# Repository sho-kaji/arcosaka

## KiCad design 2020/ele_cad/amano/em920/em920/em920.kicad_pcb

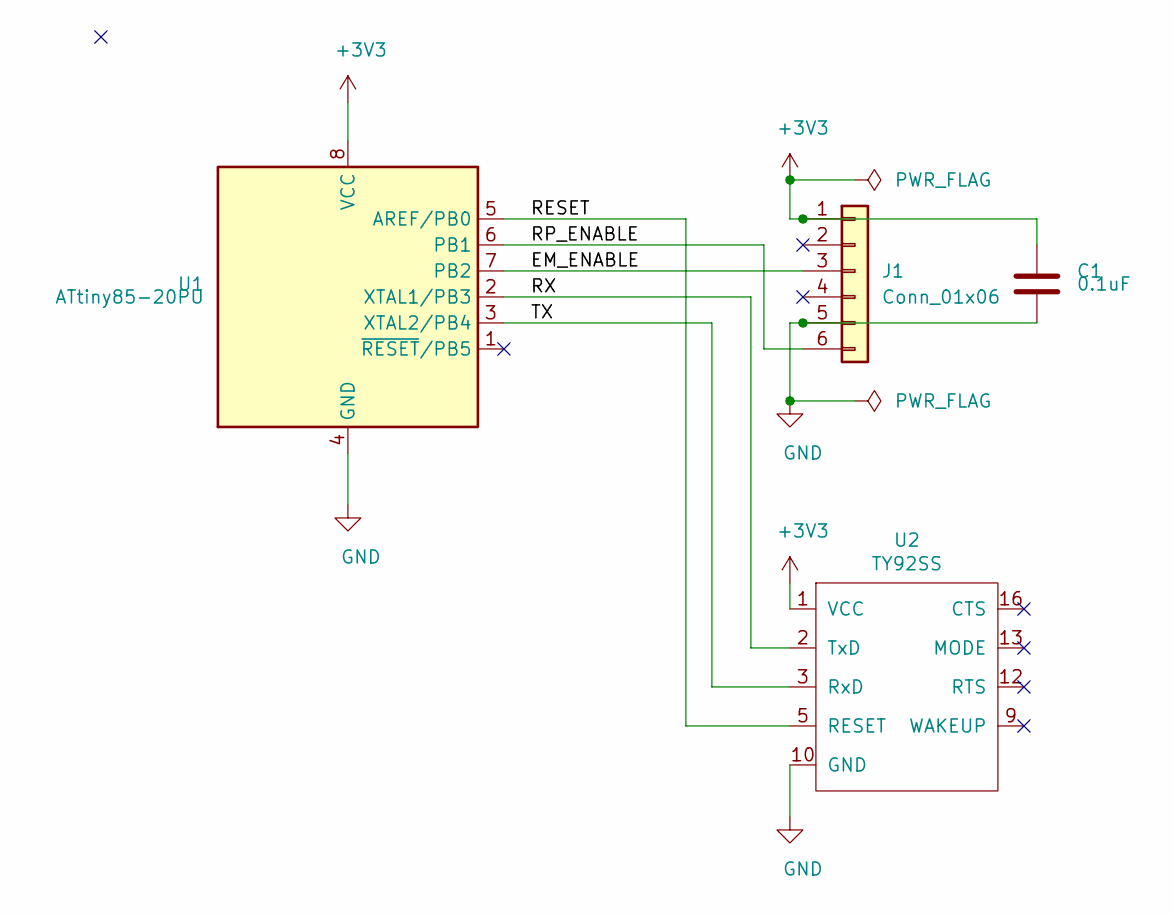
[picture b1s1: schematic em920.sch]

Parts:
C1: 0.1uF; C_Disc_D3.0mm_W1.6mm_P2.50mm
J1: Conn_01x06; PinHeader_1x06_P2.54mm_Vertical
U1: ATtiny85-20PU; DIP-8_W7.62mm
U2: TY92SS

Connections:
+3V3: C1.1, J1.1, U1.8 (VCC), U2.1 (VCC)
/EM_ENABLE: J1.3, U1.7 (PB2)
/RESET: U1.5 (AREF/PB0), U2.5 (RESET)
/RP_ENABLE: J1.6, U1.6 (PB1)
/RX: U1.2 (XTAL1/PB3), U2.2 (TxD)
/TX: U1.3 (XTAL2/PB4), U2.3 (RxD)
GND: C1.2, J1.5, U1.4 (GND), U2.10 (GND)

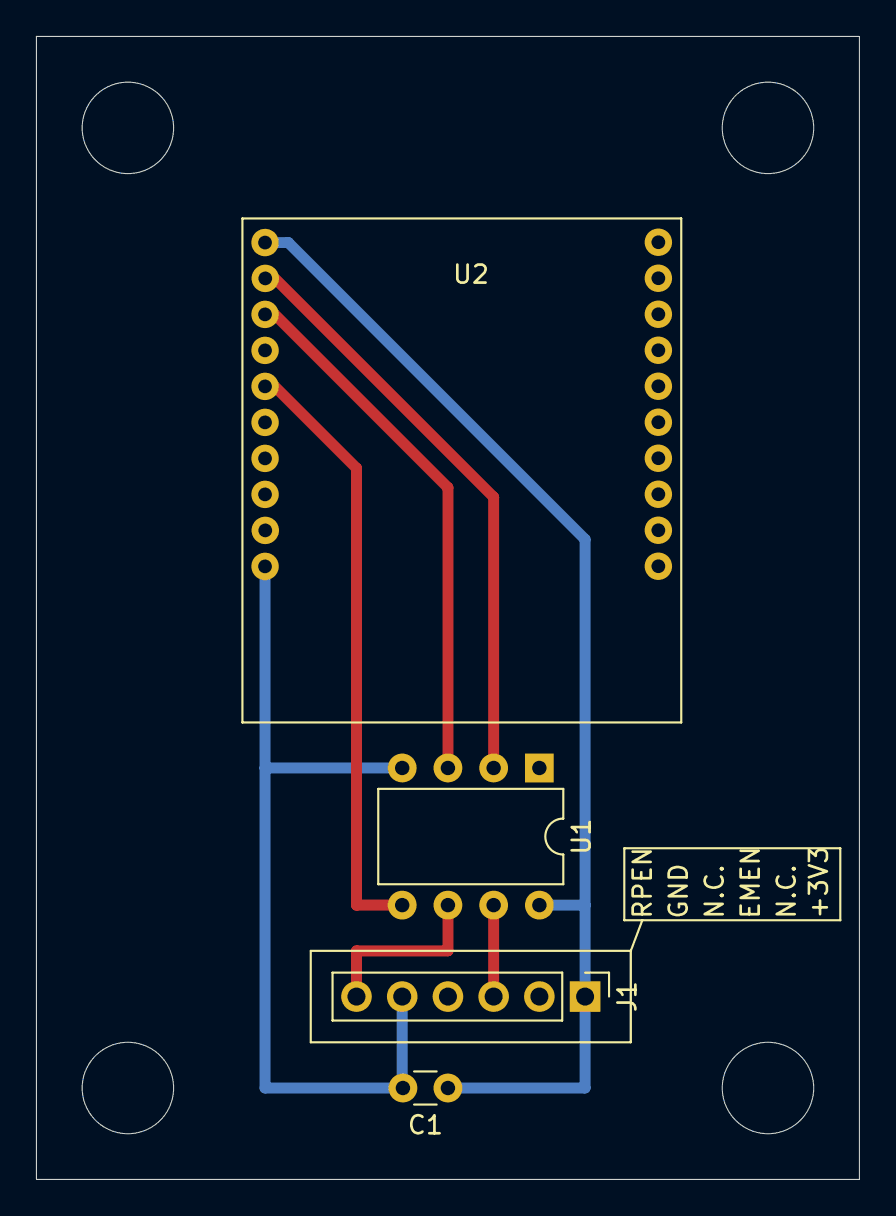
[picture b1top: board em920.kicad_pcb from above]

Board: 2 copper layers, 45.7 x 63.5 mm, 4 parts (0 on the bottom side), 7 nets.

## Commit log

2018-11-12 .gitignore 変更
2018-11-12 2018 最終版
2018-11-22 ポチのコード(らしきもの)をコミット
2019-04-27 1904272229
2019-04-28 去年のコードから自動シャットダウンスクリプトをコピー
2019-04-28 インストールスクリプト追加
2019-04-28 ROSインストールスクリプト修正
2019-04-28 ROS melodic インストールスクリプト修正
2019-04-28 スタートアップスクリプトを修正
2019-04-28 ros-melodic-desktop-full にて作成
2019-04-28 コーディングルールをreadme.txtに記載
2019-04-29 テスト用ros環境作成スクリプト
2019-04-29 テスト環境追加
2019-04-29 インストールと初期設定スクリプトをshに移動 起動スクリプトを追加
2019-04-30 test_webrtcのテスト
2019-04-30 test_webrtc monoを追加
2019-04-30 test_webrtc momoを追加/テスト成功
2019-04-30 ros_run.shを修正
2019-04-30 ファイル権限を追加
2019-04-30 ros_set.shを追加
2019-04-30 ros_setprg.shを追加
2019-04-30 test_webrtcを修正
2019-05-01 test_webrtcを修正2
2019-05-01 test_opencvを作成しようとした
2019-07-17 readmeを少し追記
2019-07-23 案山子フォルダを削除
2019-07-27 test
2019-08-14 ros_set.shの更新
2019-08-14 とりあえずテスト用に去年のarm.pyを入れてみる
2019-08-18 ros-pwm-pca9685をサブモジュールに追加
2019-09-01 とりあえず環境リセット
2019-09-01 フォルダとファイルを再構築
2019-09-01 ros_set.sh 修正
2019-09-01 ros_set.sh 修正2
2019-09-01 catkin_make修正
2019-09-01 ros_set修正3
2019-09-03 hand.py body.py テンプレート作成
2019-09-04 パッケージ名変更
2019-09-04 モーターの定数を各制御に移動
2019-09-07 arm ポート指定方法の変更
2019-09-07 arm.py 改造中
2019-09-09 コードの変更
2019-09-15 brain追加(初期化まで)
2019-09-15 不要ファイル削除
2019-09-15 モーター制御用のクラスを追加 mortor.py mortor_consts.py
2019-09-15 abh.launch 修正
2019-09-15 brain骨組み実装
2019-09-16 競合するファイルを削除
2019-09-16 実行権限付与
2019-09-16 windows用のpythonファイル実行権限スクリプト
2019-09-16 pythonのパスを指定し直し
2019-09-16 改行コード変更
2019-09-16 pythonのバージョン変更
2019-09-16 python2に合わせて修正(1)
2019-09-18 armテスト用にファイル追加
2019-09-21 モーターのテストプログラムコミット
2019-09-21 少し更新
2019-09-21 mortor_test.py 実行権限付与
2019-09-21 mortor_test 改良
2019-09-21 mortor.py 更新
2019-09-21 制限解除フラグを追加(主にテスト用)
2019-09-22 mortor 40Kのサーボつないだ
2019-09-22 doubleからintに変え忘れ
2019-09-22 DCモーター用プログラム修正
2019-09-22 DCモーター用テスト
2019-09-22 DCモーター用関数修正
2019-09-22 mortor DC用に修正
2019-09-22 mortor_const DCモーター用に調整
2019-09-22 DCモーター用
2019-09-22 DCモーター用2
2019-09-22 いろいろ更新
2019-09-22 電圧測定を追加
2019-09-22 電圧測定の権限を更新
2019-09-22 nemui
2019-09-22 やる気をなくした
2019-09-22 mortor.pyのバグ取り
2019-09-23 ステッピングモーター動いた
2019-09-23 brain動作実装(poll検出未対応)
2019-09-23 DCモーター刈リン様用テスト
2019-09-23 arm製作中
2019-09-23 param更新
2019-09-23 改行コード修正->LF
2019-09-23 arm修正
2019-09-23 mortor_test.pyで足回りテストを実行
2019-09-24 DCモーターの定数を実測したものに変更
2019-09-24 arm body hand 全面書き換え
2019-09-25 brain構文エラー修正
2019-09-26 電流測定/abhのメッセージ処理変更
2019-09-26 eyes.py コミット
2019-09-26 abhを変更
2019-09-26 実行権限付与(いつも忘れる)
2019-09-26 先頭を「#!/usr/bin/env python」に変更
2019-09-26 body_const更新
2019-09-26 芽かきと収穫の動作を追加
2019-09-26 brain ポール検出時動作追加、コメント追加、バグ修正
2019-09-26 brain バグ修正
2019-09-26 eye 先頭コメント追加
2019-09-27 とりあえずコミット
2019-09-27 とりあえず動いたから更新
2019-09-27 ina226電流測定追加
2019-09-27 brainバグ修正
2019-09-27 brain バグ修正、デバッグモードコメント追加
2019-09-27 ダミーclient追加
2019-09-28 arm body handを統合
2019-09-28 abh_constsの実行権限付与
2019-10-04 eye通信部分実装(仕組みのみ)
2019-10-04 モーター制御の微調整
2019-10-05 360サーボのテスト用
2019-10-05 電流電圧測定修正
2019-10-05 距離センサーテストモジュール追加
2019-10-05 python2.7では精度が出ない
2019-10-05 電圧低下時の動作を追加
2019-10-05 ミス修正
2019-10-05 シャットダウン判定修正
2019-10-12 debug Arm用部分だけ作成しました。
    下記をinstallしてください
    sudo apt-get instgall ros-melodic-roswww
    その後、catkin_makeしてください。
    下記を実行してください
    roslaunch arc2019 client.launch
    下記アドレスにアクセスしてください。
2019-10-13 コメント追加
2019-10-13 電流電圧をbodyから流せるように変更
2019-10-13 今日の作業をコミット
2019-10-13 今日の作業をコミット2
2019-10-14 各センサーがついていない場合にデバッグモードで動くようにした(はず)
2019-10-15 camera画像が映るようにしました。
    1.mjpg-streamerをinstallしてください。
    手順
    $ git clone https://github.com/jacksonliam/mjpg-streamer.git
    $ cd mjpg-streamer/mjpg-streamer-experimental
    $ make
    $ sudo make install
2019-10-15 コミット漏れファイルを追加
2019-10-15 コミット漏れ2
2019-10-15 mortor.py 変更
2019-10-15 mortor.pyの関数を変更
2019-10-18 eventemitter2.min.js roslib.min.js をサーバー呼び出しに変更
2019-10-18 全操作ページのページだけ実装 brainへのmode,targetコマンドは送信可能
    未実装
    manual の hand 操作ボタン
    footの操作ボタン（全部）
2019-10-18 バッテリー情報をbodyから送信するように変更
2019-10-18 mortor.py 修正
2019-10-19 mortor_test.pyとか修正
2019-10-19 距離センサークラス追加
2019-10-19 バグ修正
2019-10-19 ina226 終了処理を変更
2019-10-20 全画面実装時のデバッグ部分コミット漏れ
2019-10-20 footコードを実装 *距離センサとdebugには未対応
2019-10-20 ソフトPWMにしたつもり
2019-10-20 camera.sh 修正
2019-10-21 camera.shを修正(未確認)
2019-10-21 camera.sh 少し修正
2019-10-21 サーボモーターの調整とか
2019-10-22 pca9685ドライバを作成 ファイルのインデント調整
2019-10-22 ファイルに実行権限付与
2019-10-22 モーター回り変更
2019-10-22 launchファイル変更
2019-10-22 mjpg_streamerの起動タイミングを変更
2019-10-22 camera.sh 解像度変更
2019-10-22 初期化処理修正
2019-10-26 いろいろ修正
2019-10-27 モーター系を修正
2019-11-02 msgとconstの修正
2019-11-02 eyes更新
2019-11-02 communication between html-abh
2019-11-02 communication between html-foot
2019-11-02 abh.py 修正
2019-11-02 html slideber->numberbox
2020-05-08 -2019を元に2020の作業ディレクトリを作成 不要なファイルはおいおい削除する -Dockerfileの登録
2020-05-09 README.mdを加筆修正
2020-05-16 sample用のled点灯パッケージの登録
2020-05-16 README 微修正
2020-08-16 最新版だとarm対応してないようなのでmelodicに固定
2020-09-13 2019のファイルを2019Directoryに移動 足回り用にfoot directory作成 各担当はscripts directoryの下に開発directoryを作成して作業するとよさそう + pathはrosが頑張って探してくれるらしい。。
2020-09-13 エレキ班のIOポート表からGPIOの定義ファイルを作成
2020-09-26 プッシュテスト
2020-09-26 プッシュテスト(削除)
2020-09-26 提出用IO表に合わせてGPIO定義ファイル修正
2020-09-26 モジュール追加練習
2020-10-06 電圧電流測定モジュールの追加
2020-10-11 電圧電流測定モジュール更新
2020-10-17 Dockerfile更新
2020-12-04 アームモジュール追加
2020-12-05 電圧電流測定モジュール追加
2020-12-05 Webアプリ受信側サンプル追加(SW状態表示)
2020-12-06 ‘電圧電流表示てすと’
2020-12-07 Webアプリ画面のアップロード(暫定)
2021-01-23 arm暫定部品更新(注：mainができ次第Subscribe設定をあわせること)
2021-01-23 電圧電流測定、緊急停止デバッグアプリ整理
2021-01-31 デバッグ画面のコミット(処理未実装)
2021-02-05 armdebug更新
2021-02-05 i register enviroment for ros + sqlite3
2021-02-05 Regist environment for ros + sqlite3
2021-02-27 日本語ファイル名を英文に変更
2021-02-27 走行距離表示箇所の修正
2021-03-06 変更漏れ
2021-03-06 変更漏れ対応
2021-03-06 メモの変更、デバッグボタンの追加、不具合修正
2021-04-02 armdebug修正
2021-04-02 ロータリエンコーダモジュール追加
2021-04-02 実行可能(+x)に修正
2021-04-03 smbus追加
2021-04-03 motor修正
2021-04-03 自動スタート用シェル追加
2021-04-03 autostart.sh修正
2021-04-10 電流電圧モジュール修正
2021-04-10 入力テキストラッチ処理追加
2021-04-10 commit for dc motor debug software Not tested
2021-04-11 Create debug_botton.jpg
    img add
2021-04-17 loginのif実装
    loginのif実装
2021-04-17 アームモジュールレベルアップ
2021-05-16 ログイン画面のデモを作成(表示だけ)
2021-05-28 modified UI for foot debug
2021-05-30 README.md: docker run で port設定変更 他追記 dc_motor.py: pigpioのonoffスイッチ追加 Dockerfile: docker run時にcatkin_makeするように修正
2021-05-30 Dockerfile : 不要な修正を削除
2021-06-01 距離センサ値表示対応
2021-06-12 ライントレース変換基板のテストプログラム作成
2021-06-12 created i2c_sensor code
2021-06-12 docker for desktop とのコンパチ用のpigpioスイッチファイル追加
2021-06-12 __pigpio__の設定ミス修正
2021-06-19 ステッピングモータモジュール微修正
2021-06-20 ライントレースセンサモジュール修正
2021-07-10 ロータリエンコーダモジュール ピン番号修正
2021-07-16 各ディレクトリの2019年のファイルを分離
2021-07-16 デバッグ用メイン追加(web⇔main⇔arm,footの接続確認済み)
2021-07-17 画面遷移バグ修正(仕様変更はまだ入れていない)
2021-07-17 docker run 記載復元
2021-07-17 画面仕様変更(javascript処理は後日実装)
2021-07-19 IF設計書の全msgファイルを反映
2021-07-20 database.msg修正
2021-07-21 メインモジュール追加
2021-07-22 データベース更新 渡辺 梶
2021-07-23 sonor修正 移動平均を取得して変換するように修正 author tabichi
2021-07-24 測距センサの外れ値の除外実装 ブレが+-1cm 最短距離が4cm 田渕
2021-07-27 エレキのCADデータをコミット(em920_remoteは未完)
2021-07-29 緊急停止リモコンのデータ更新
2021-07-29 データベース修正
2021-08-07 緊急停止リモコンの更新
2021-08-11 回路データの更新
2021-08-14 データベース更新
2021-08-14 緊急停止リモコンの回路更新
2021-08-14 メッセージ追加
2021-08-14 リモコンのDCDCを昇降圧に変更
2021-08-23 em920のフォルダ構造を変更
2021-08-27 foot モジュール本番用初回登録 未動作確認
2021-08-28 dc_motorのdebug動作版登録
2021-08-28 デバッグ結果反映
2021-09-04 foot: motor停止時の入力値を0に設定
2021-09-11 ライブラリリンクの削除
2021-09-11 ライブラリリンクの追加
2021-09-11 ライブラリの更新
2021-09-18 アームモジュール更新
2021-09-24 html にrosの対応組み込み。 startまでだが一旦登録 リロードや戻るの機能があやしい
2021-09-25 html 更新
2022-04-09 Colaboratory を使用して作成しました
